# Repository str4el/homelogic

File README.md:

Homelogic
---------

Die Homelogic ist eine dezentral arbeitende __SPS Steuerung__, die für den Hausgebrauch gedacht ist. Es gibt verschiedene Hardware die mit der selben Firmware laufen. Die meisten sind für den direktem betrieb am Netz ausgelegt und haben mehrere digitale Ein- und Ausgänge.

Das Projekt besteht aus den Plänen für die _Hardware_, der _Firmware_ darin, einer _Bibliothek_ und einen darauf aufbauendem _Steuerprogramm_.

Die Steuerung ist SPS typisch frei programmierbar, als Sprache kommt dafür eine Variante von _Anweisungsliste_ zum Einsatz.

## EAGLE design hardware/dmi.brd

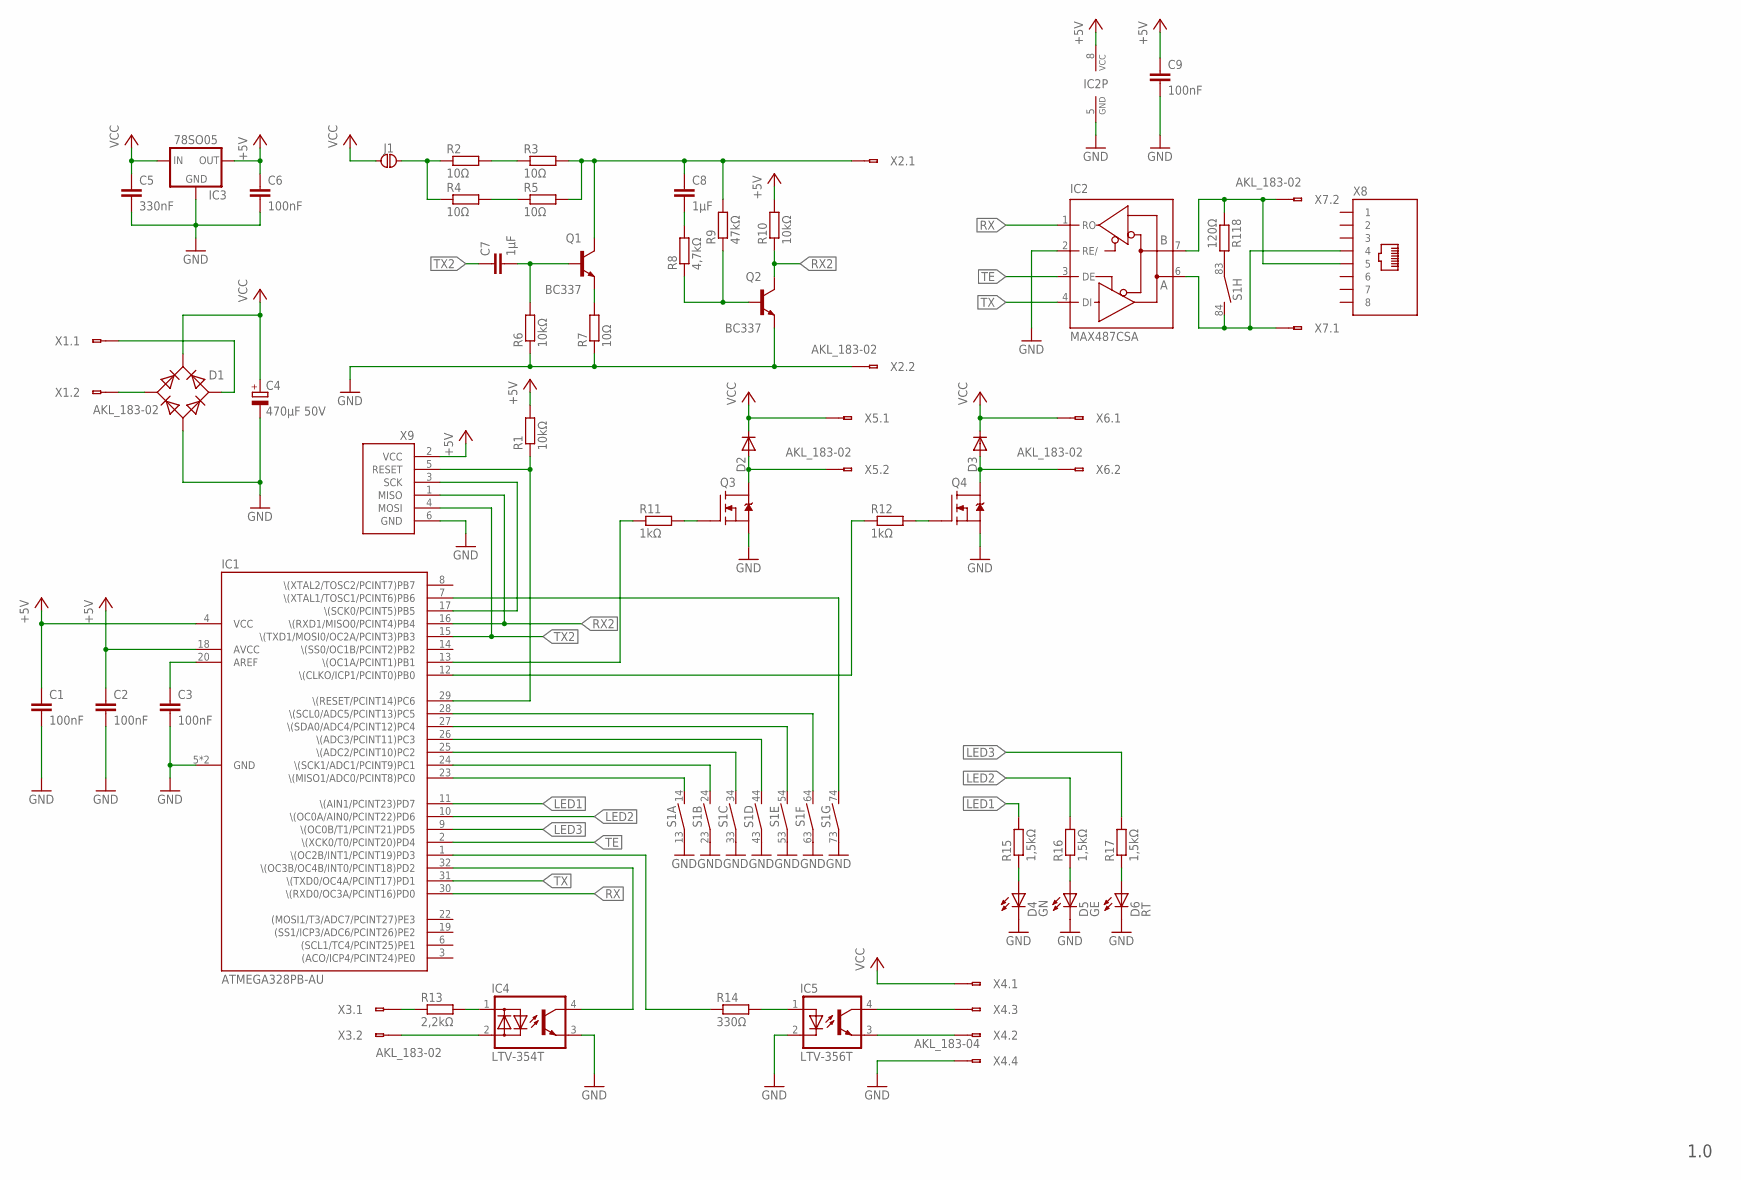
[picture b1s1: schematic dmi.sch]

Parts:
C1, C2, C3, C9: 100nF; CHIP_0603
C4: 470μF 50V; E5-13
C5: 330nF; CHIP_0805
C6: 100nF; CHIP_0805
C7, C8: 1μF; CHIP_1206
D1: GLEICHRICHTER-SDIP; SDIP04_508
D2, D3: DIODE-SOD123; SOD123
D4: GN; CHIP_0805
D5: GE; CHIP_0805
D6: RT; CHIP_0805
IC1: ATMEGA328PB-AU; QFP32_08
IC2: MAX487CSA; SOP08_127
IC3: 78SO05; SOP08_127
IC4: LTV-354T; SOP04_254
IC5: LTV-356T; SOP04_254
J1: JUMPER; JUMPER2
Q1, Q2: BC337; SOT23
Q3, Q4: N-MOS-SOT23-GSD; SOT23
R1, R6, R10: 10kΩ; CHIP_0603
R2, R3, R4, R5, R7: 10Ω; CHIP_1206
R8: 4,7kΩ; CHIP_0603
R9: 47kΩ; CHIP_0603
R11, R12: 1kΩ; CHIP_0603
R13: 2,2kΩ; CHIP_0603
R14: 330Ω; CHIP_0603
R15, R16, R17: 1,5kΩ; CHIP_0603
R118: 120Ω; CHIP_0805
S1: DP08D; DIP08_SMD
X1, X2, X3, X5, X6, X7: AKL_183-02
X4: AKL_183-04
X8: 8P8C; C-BMJ-0102
X9: ISP-AVR6; ML6

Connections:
+5V: C1.1, C2.1, C6.1, C9.1, IC1.4 (VCC), IC1.18 (AVCC), IC2.8 (VCC), IC3.1 (OUT), R1.2, R10.2, X9.2 (VCC)
GND: C1.2, C2.2, C3.2, C4.-, C5.2, C6.2, C9.2, D1.2 (-), D4.2 (C), D5.2 (C), D6.2 (C), IC1.5 (GND), IC1.21 (GND), IC2.2 (RE/), IC2.5 (GND), IC3.2 (GND), IC3.3 (GND), IC3.6 (GND), IC3.7 (GND), IC4.3 (E), IC5.2 (K), Q2.2 (E), Q3.2 (S), Q4.2 (S), R6.1, R7.1, S1.13 (3), S1.23 (3), S1.33 (3), S1.43 (3), S1.53 (3), S1.63 (3), S1.73 (3), X2.2, X4.4, X9.6 (GND)
LED1: IC1.11 (\(AIN1/PCINT23)PD7), R15.2
LED2: IC1.10 (\(OC0A/AIN0/PCINT22)PD6), R16.2
LED3: IC1.9 (\(OC0B/T1/PCINT21)PD5), R17.2
unnamed: IC1.32 (\(OC3B/OC4B/INT0/PCINT18)PD2), IC4.4 (C)
unnamed: IC4.2 (K), X3.2
unnamed: IC2.6 (A), S1.84 (4), X7.1, X8.P$4 (4)
unnamed: IC1.29 (\(RESET/PCINT14)PC6), R1.1, X9.5 (RESET)
unnamed: IC1.13 (\(OC1A/PCINT1)PB1), R11.1
unnamed: Q3.1 (G), R11.2
unnamed: D2.A, Q3.3 (D), X5.2
unnamed: IC5.3 (E), X4.2
unnamed: IC5.4 (C), X4.3
unnamed: IC1.1 (\(OC2B/INT1/PCINT19)PD3), R14.1
unnamed: IC5.1 (A), R14.2
unnamed: J1.P$2, R2.1, R4.1
unnamed: R2.2, R3.1
unnamed: R13.1, X3.1
unnamed: IC4.1 (A), R13.2
unnamed: Q1.2 (E), R7.2
unnamed: C7.2, Q1.1 (B), R6.2
unnamed: Q2.1 (B), R8.1, R9.1
unnamed: C8.2, R8.2
unnamed: D1.4 (AC2), X1.1
unnamed: C8.1, Q1.3 (C), R3.2, R5.2, R9.2, X2.1
unnamed: D1.3 (AC1), X1.2
unnamed: R4.2, R5.1
unnamed: Q4.1 (G), R12.2
unnamed: D3.A, Q4.3 (D), X6.2
unnamed: IC1.12 (\(CLKO/ICP1/PCINT0)PB0), R12.1
unnamed: IC2.7 (B), R118.1, X7.2, X8.P$5 (5)
unnamed: IC1.23 (\(MISO1/ADC0/PCINT8)PC0), S1.14 (4)
unnamed: IC1.24 (\(SCK1/ADC1/PCINT9)PC1), S1.24 (4)
unnamed: IC1.25 (\(ADC2/PCINT10)PC2), S1.34 (4)
unnamed: IC1.26 (\(ADC3/PCINT11)PC3), S1.44 (4)
unnamed: IC1.27 (\(SDA0/ADC4/PCINT12)PC4), S1.54 (4)
unnamed: R118.2, S1.83 (3)
unnamed: IC1.28 (\(SCL0/ADC5/PCINT13)PC5), S1.64 (4)
unnamed: IC1.7 (\(XTAL1/TOSC1/PCINT6)PB6), S1.74 (4)
unnamed: D6.1 (A), R17.1
unnamed: IC1.17 (\(SCK0/PCINT5)PB5), X9.3 (SCK)
unnamed: C3.1, IC1.20 (AREF)
unnamed: D4.1 (A), R15.1
unnamed: D5.1 (A), R16.1
RX: IC1.30 (\(RXD0/OC3A/PCINT16)PD0), IC2.1 (RO)
RX2: IC1.16 (\(RXD1/MISO0/PCINT4)PB4), Q2.3 (C), R10.1, X9.1 (MISO)
TE: IC1.2 (\(XCK0/T0/PCINT20)PD4), IC2.3 (DE)
TX: IC1.31 (\(TXD0/OC4A/PCINT17)PD1), IC2.4 (DI)
TX2: C7.1, IC1.15 (\(TXD1/MOSI0/OC2A/PCINT3)PB3), X9.4 (MOSI)
VCC: C4.+, C5.1, D1.1 (+), D2.K, D3.K, IC3.8 (IN), J1.P$1, X4.1, X5.1, X6.1

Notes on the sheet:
1.0

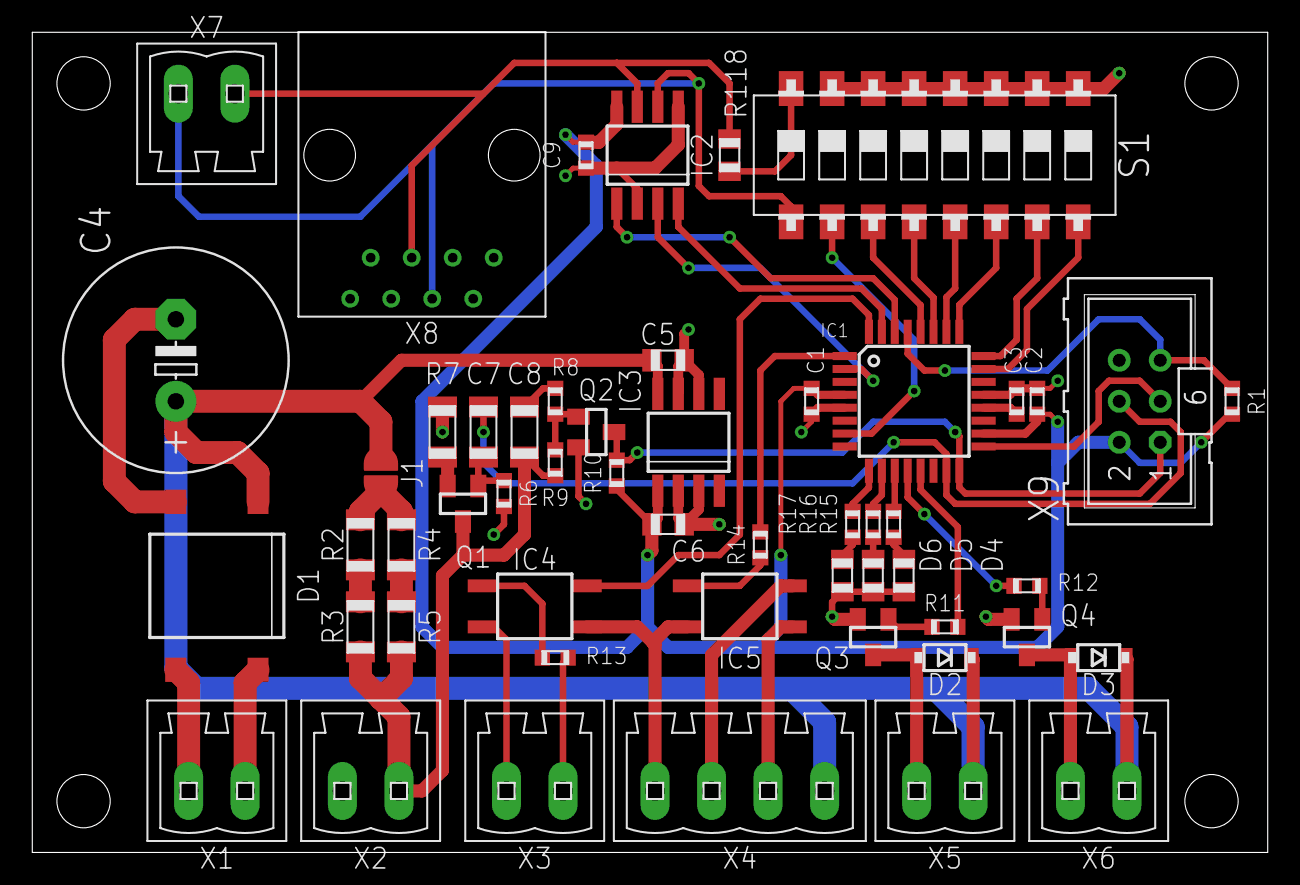
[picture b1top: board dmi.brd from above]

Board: 2 copper layers, 76.5 x 50.8 mm, 53 parts (0 on the bottom side), 51 nets.

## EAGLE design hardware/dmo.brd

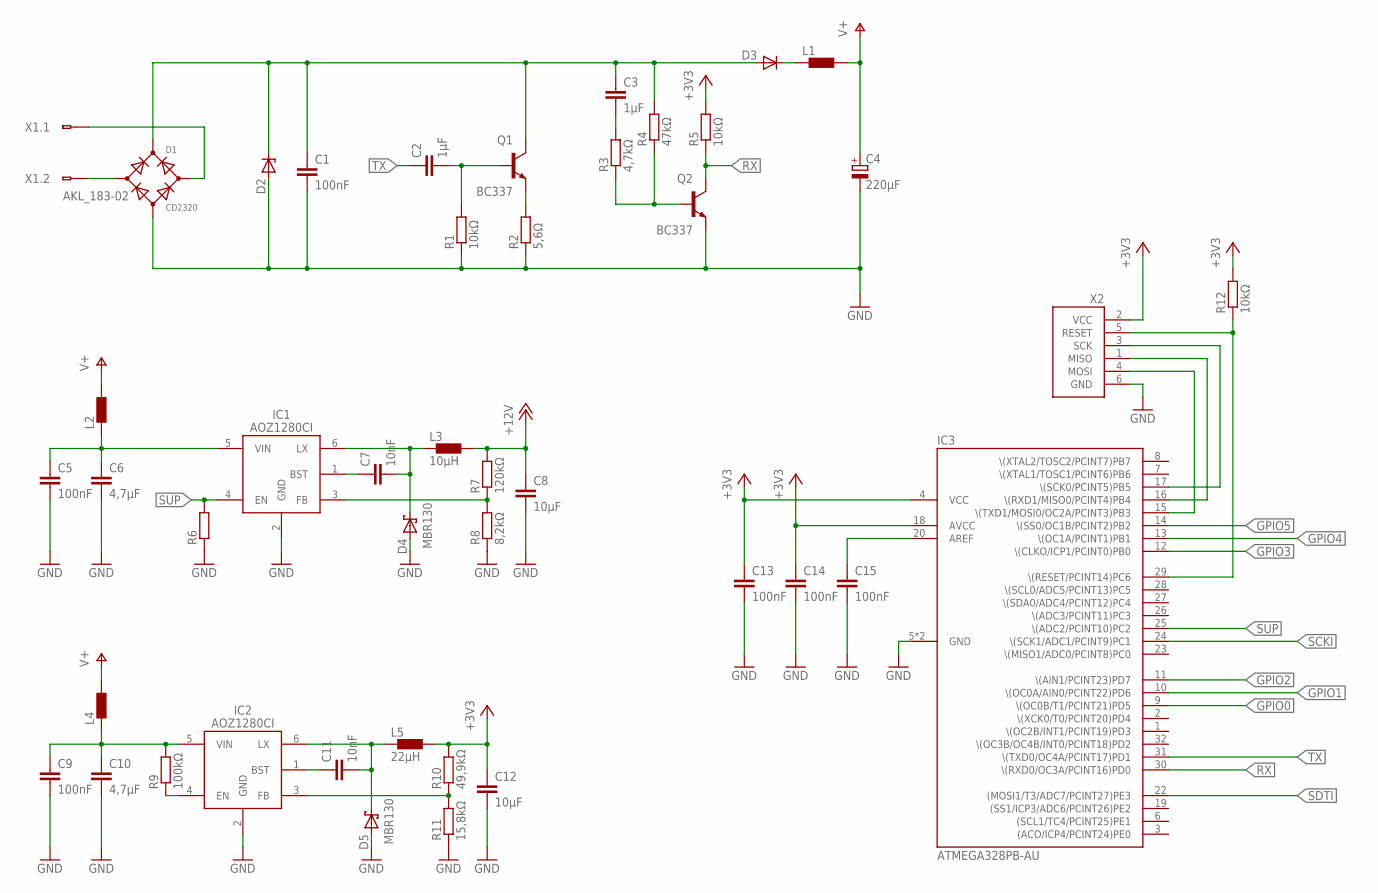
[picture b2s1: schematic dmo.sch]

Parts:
C1: 100nF; CHIP_1206
C2, C3: 1μF; CHIP_1206
C4: 220μF; E5-13
C5, C9: 100nF; CHIP_0805
C6, C10: 4,7μF; CHIP_1206
C7, C11: 10nF; CHIP_0603
C8, C12: 10μF; CHIP_1206
C13, C14, C15: 100nF; CHIP_0603
D1: CD2320; 2320
D2: Z-DIODE-SOD123; SOD123
D3: DIODE-SOD123; SOD123
D4, D5: MBR130; SOD123
IC1, IC2: AOZ1280CI; SOT23-6_095
IC3: ATMEGA328PB-AU; QFP32_08
L1, L2, L4: L_0805; CHIP_0805
L3: 10μH; CHIP_1210
L5: 22μH; CHIP_0805
Q1, Q2: BC337; SOT23
R1, R5, R12: 10kΩ; CHIP_0603
R2: 5,6Ω; CHIP_1206
R3: 4,7kΩ; CHIP_0603
R4: 47kΩ; CHIP_0603
R6: R_0603; CHIP_0603
R7: 120kΩ; CHIP_0603
R8: 8,2kΩ; CHIP_0603
R9: 100kΩ; CHIP_0603
R10: 49,9kΩ; CHIP_0603
R11: 15,8kΩ; CHIP_0603
X1: AKL_183-02
X2: ISP-AVR6; ML6

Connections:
+3V3: C12.1, C13.1, C14.1, IC3.4 (VCC), IC3.18 (AVCC), L5.1, R5.2, R10.2, R12.2, X2.2 (VCC)
+12V: C8.1, L3.1, R7.2
GND: C1.2, C4.-, C5.2, C6.2, C8.2, C9.2, C10.2, C12.2, C13.2, C14.2, C15.2, D1.-, D2.A, D4.A, D5.A, IC1.2 (GND), IC2.2 (GND), IC3.5 (GND), IC3.21 (GND), Q2.2 (E), R1.1, R2.1, R6.1, R8.1, R11.1, X2.6 (GND)
GPIO0: IC3.9 (\(OC0B/T1/PCINT21)PD5)
GPIO1: IC3.10 (\(OC0A/AIN0/PCINT22)PD6)
GPIO2: IC3.11 (\(AIN1/PCINT23)PD7)
GPIO3: IC3.12 (\(CLKO/ICP1/PCINT0)PB0)
GPIO4: IC3.13 (\(OC1A/PCINT1)PB1)
GPIO5: IC3.14 (\(SS0/OC1B/PCINT2)PB2)
unnamed: IC3.16 (\(RXD1/MISO0/PCINT4)PB4), X2.1 (MISO)
unnamed: IC3.15 (\(TXD1/MOSI0/OC2A/PCINT3)PB3), X2.4 (MOSI)
unnamed: D3.K, L1.2
unnamed: IC3.17 (\(SCK0/PCINT5)PB5), X2.3 (SCK)
unnamed: IC3.29 (\(RESET/PCINT14)PC6), R12.1, X2.5 (RESET)
unnamed: IC2.4 (EN), R9.1
unnamed: C11.1, IC2.1 (BST)
unnamed: C11.2, D5.K, IC2.6 (LX), L5.2
unnamed: IC2.3 (FB), R10.1, R11.2
unnamed: C9.1, C10.1, IC2.5 (VIN), L4.2, R9.2
unnamed: C7.1, IC1.1 (BST)
unnamed: C7.2, D4.K, IC1.6 (LX), L3.2
unnamed: IC1.3 (FB), R7.1, R8.2
unnamed: C5.1, C6.1, IC1.5 (VIN), L2.2
unnamed: C15.1, IC3.20 (AREF)
unnamed: Q1.2 (E), R2.2
unnamed: C2.2, Q1.1 (B), R1.2
unnamed: Q2.1 (B), R3.1, R4.1
unnamed: C3.2, R3.2
unnamed: D1.AC2, X1.1
unnamed: D1.AC1, X1.2
RX: IC3.30 (\(RXD0/OC3A/PCINT16)PD0), Q2.3 (C), R5.1
SCKI: IC3.24 (\(SCK1/ADC1/PCINT9)PC1)
SDTI: IC3.22 ((MOSI1/T3/ADC7/PCINT27)PE3)
SUP: IC1.4 (EN), IC3.25 (\(ADC2/PCINT10)PC2), R6.2
TX: C2.1, IC3.31 (\(TXD0/OC4A/PCINT17)PD1)
V+: C4.+, L1.1, L2.1, L4.1
VCC: C1.1, C3.1, D1.+, D2.K, D3.A, Q1.3 (C), R4.2

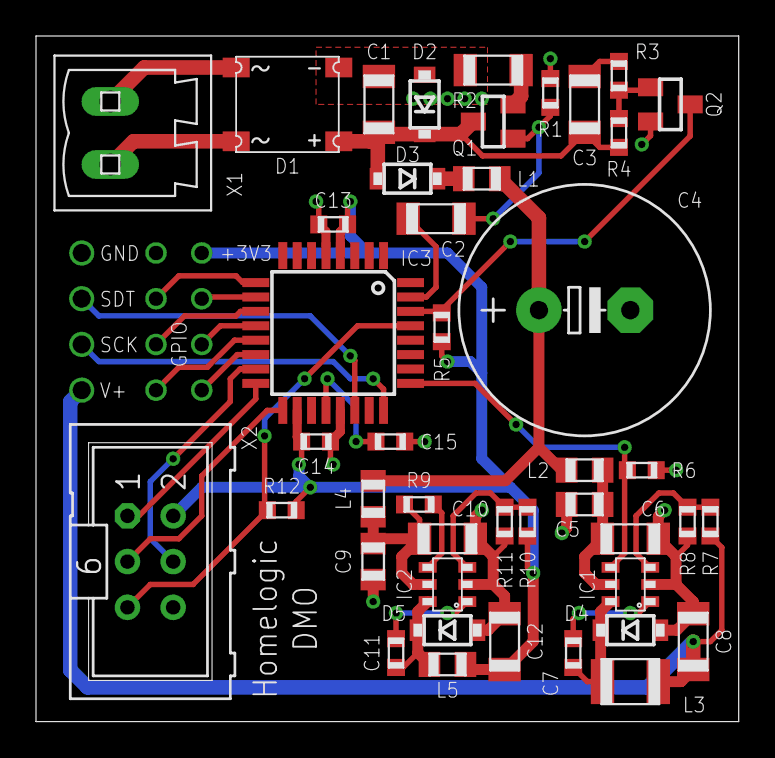
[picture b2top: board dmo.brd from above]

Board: 2 copper layers, 39.0 x 38.1 mm, 44 parts (0 on the bottom side), 29 nets.

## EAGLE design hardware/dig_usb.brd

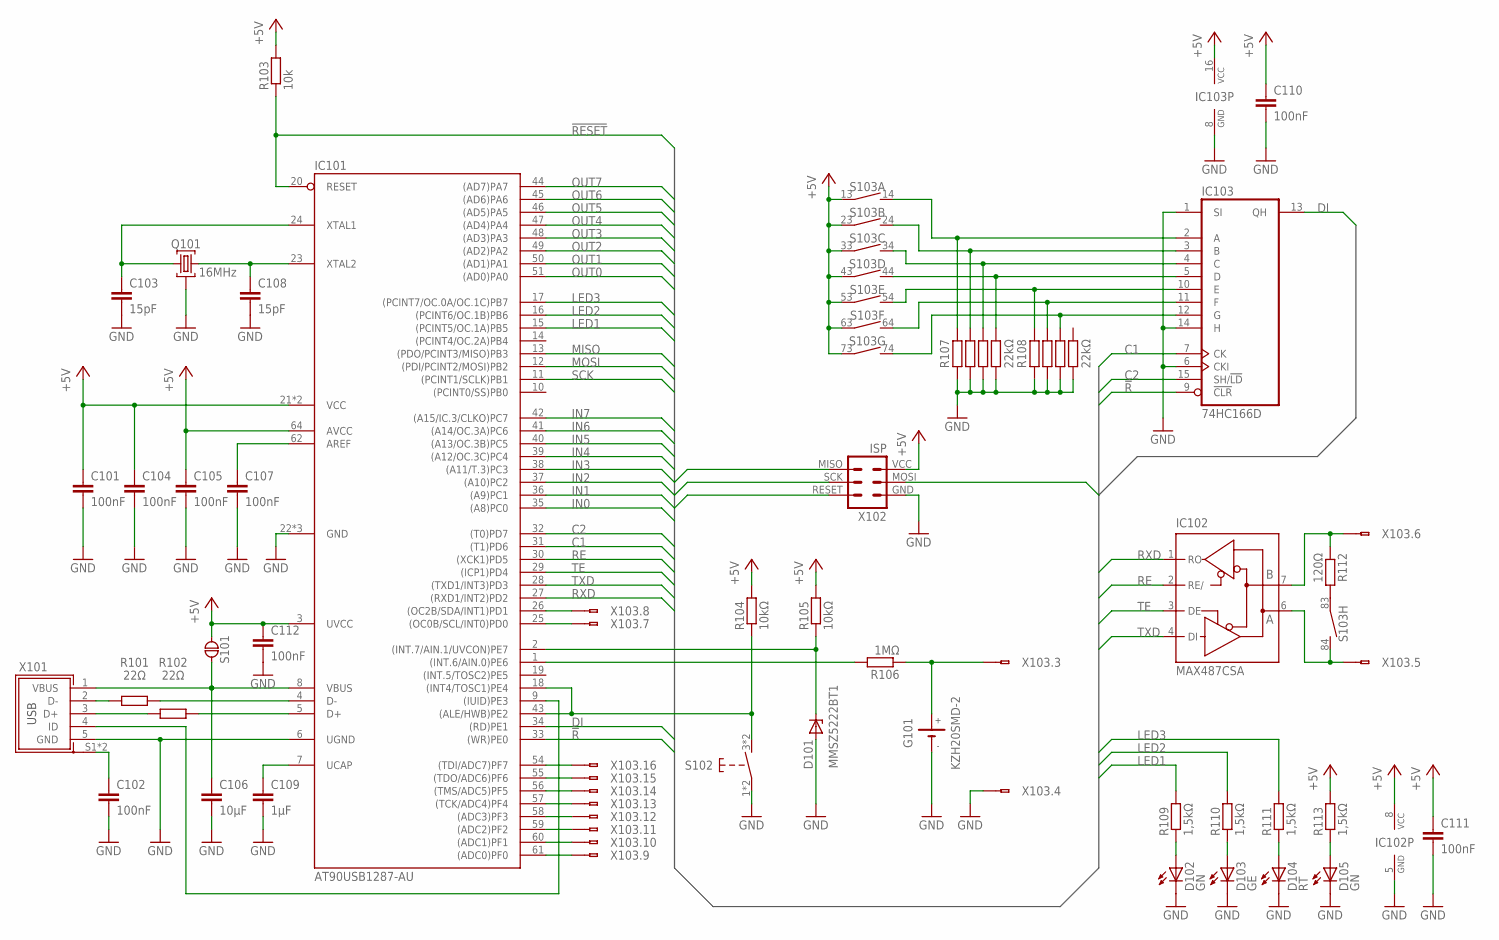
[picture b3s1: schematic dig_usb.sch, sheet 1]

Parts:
C101, C104, C105, C107, C110, C111, C112: 100nF; CHIP_0603
C102: 100nF; CHIP_0805
C103, C108: 15pF; CHIP_0805
C106: 10μF; CHIP_0805
C109: 1μF; CHIP_0805
D101: MMSZ5222BT1; SOD123
D102, D105: GN; CHIP_0805
D103: GE; CHIP_0805
D104: RT; CHIP_0805
G101: KZH20SMD-2; KHZ20SMD-2
IC101: AT90USB1287-AU; QFP64_08
IC102: MAX487CSA; SOP08_127
IC103: 74HC166D; SOP16_127
Q101: 16MHz; X22
R101, R102: 22Ω; CHIP_0805
R103: 10k; CHIP_0805
R104, R105: 10kΩ; CHIP_0805
R106: 1MΩ; CHIP_0805
R107, R108: 22kΩ; 1206
R109, R110, R111, R113: 1,5kΩ; CHIP_0805
R112: 120Ω; CHIP_0805
S101: JUMPER; JUMPER2
S102: KURZHUBS1; SCHURTER1301
S103: DP08D; DIP08_SMD
X101: USB-MINI-V; WE651005136421
X102: ISP; ML6
X103: WS34V

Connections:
!R: IC101.33 ((WR)PE0), IC103.9 (!CLR)
!RESET: IC101.20 (RESET), R103.1, X102.RESET
+5V: C101.1, C104.1, C105.1, C110.1, C111.1, C112.1, IC101.3 (UVCC), IC101.21 (VCC), IC101.52 (VCC), IC101.64 (AVCC), IC102.8 (VCC), IC103.16 (VCC), R103.2, R104.2, R105.2, R113.2, S101.P$1, S103.13 (3), S103.23 (3), S103.33 (3), S103.43 (3), S103.53 (3), S103.63 (3), S103.73 (3), X102.VCC; also elsewhere on the board
C1: IC101.31 ((T1)PD6), IC103.7 (CK)
C2: IC101.32 ((T0)PD7), IC103.15 (SH/!LD)
DI: IC101.34 ((RD)PE1), IC103.13 (QH)
GND: C101.2, C102.2, C103.2, C104.2, C105.2, C106.2, C107.2, C108.2, C109.2, C110.2, C111.2, C112.2, D101.A, D102.2 (C), D103.2 (C), D104.2 (C), D105.2 (C), G101.-, IC101.6 (UGND), IC101.22 (GND), IC101.53 (GND), IC101.63 (GND), IC102.5 (GND), IC103.1 (SI), IC103.6 (CKI), IC103.8 (GND), IC103.14 (H), Q101.2 (G), Q101.4 (G), R107.1A (1), R107.2A (3), R107.3A (5), R107.4A (7), R108.1A (1), R108.2A (3), R108.3A (5), R108.4A (7), S102.1, S102.2, X101.5 (GND), X102.GND, X103.4; also elsewhere on the board
IN0: IC101.35 ((A8)PC0); also elsewhere on the board
IN1: IC101.36 ((A9)PC1); also elsewhere on the board
IN2: IC101.37 ((A10)PC2); also elsewhere on the board
IN3: IC101.38 ((A11/T.3)PC3); also elsewhere on the board
IN4: IC101.39 ((A12/OC.3C)PC4); also elsewhere on the board
IN5: IC101.40 ((A13/OC.3B)PC5); also elsewhere on the board
IN6: IC101.41 ((A14/OC.3A)PC6); also elsewhere on the board
IN7: IC101.42 ((A15/IC.3/CLKO)PC7); also elsewhere on the board
LED1: IC101.15 ((PCINT5/OC.1A)PB5), R109.2
LED2: IC101.16 ((PCINT6/OC.1B)PB6), R110.2
LED3: IC101.17 ((PCINT7/OC.0A/OC.1C)PB7), R111.2
MISO: IC101.13 ((PDO/PCINT3/MISO)PB3), X102.MISO
MOSI: IC101.12 ((PDI/PCINT2/MOSI)PB2), X102.MOSI
unnamed: D104.1 (A), R111.1
unnamed: C107.1, IC101.62 (AREF)
unnamed: IC102.6 (A), S103.84 (4), X103.5
unnamed: IC101.1 ((INT.6/AIN.0)PE6), R106.2
unnamed: IC102.7 (B), R112.1, X103.6
unnamed: IC103.2 (A), R107.1B (2), S103.14 (4)
unnamed: IC103.3 (B), R107.2B (4), S103.24 (4)
unnamed: IC103.4 (C), R107.3B (6), S103.34 (4)
unnamed: IC103.5 (D), R107.4B (8), S103.44 (4)
unnamed: IC103.10 (E), R108.1B (2), S103.54 (4)
unnamed: IC103.11 (F), R108.2B (4), S103.64 (4)
unnamed: IC103.12 (G), R108.3B (6), S103.74 (4)
unnamed: R112.2, S103.83 (3)
unnamed: D105.1 (A), R113.1
unnamed: D102.1 (A), R109.1
unnamed: D103.1 (A), R110.1
unnamed: C109.1, IC101.7 (UCAP)
unnamed: R102.1, X101.3 (D+)
unnamed: IC101.5 (D+), R102.2
unnamed: R101.1, X101.2 (D-)
unnamed: IC101.4 (D-), R101.2
unnamed: IC101.9 ((IUID)PE3), X101.4 (ID)
unnamed: C106.1, IC101.8 (VBUS), S101.P$2, X101.1 (VBUS)
unnamed: C108.1, IC101.23 (XTAL2), Q101.3 (2)
unnamed: C103.1, IC101.24 (XTAL1), Q101.1
unnamed: D101.K, IC101.2 ((INT.7/AIN.1/UVCON)PE7), R105.1
unnamed: IC101.61 ((ADC0)PF0), X103.9
unnamed: IC101.60 ((ADC1)PF1), X103.10
unnamed: IC101.59 ((ADC2)PF2), X103.11
unnamed: IC101.58 ((ADC3)PF3), X103.12
unnamed: IC101.57 ((TCK/ADC4)PF4), X103.13
unnamed: IC101.56 ((TMS/ADC5)PF5), X103.14
unnamed: IC101.55 ((TDO/ADC6)PF6), X103.15
unnamed: IC101.54 ((TDI/ADC7)PF7), X103.16
unnamed: G101.+, R106.1, X103.3
unnamed: IC101.25 ((OC0B/SCL/INT0)PD0), X103.7
unnamed: IC101.26 ((OC2B/SDA/INT1)PD1), X103.8
unnamed: IC101.18 ((INT4/TOSC1)PE4), IC101.43 ((ALE/HWB)PE2), R104.1, S102.3 (S), S102.4 (S)
OUT0: IC101.51 ((AD0)PA0); also elsewhere on the board
OUT1: IC101.50 ((AD1)PA1); also elsewhere on the board
OUT2: IC101.49 ((AD2)PA2); also elsewhere on the board
OUT3: IC101.48 ((AD3)PA3); also elsewhere on the board
OUT4: IC101.47 ((AD4)PA4); also elsewhere on the board
OUT5: IC101.46 ((AD5)PA5); also elsewhere on the board
OUT6: IC101.45 ((AD6)PA6); also elsewhere on the board
OUT7: IC101.44 ((AD7)PA7); also elsewhere on the board
RE: IC101.30 ((XCK1)PD5), IC102.2 (RE/)
RXD: IC101.27 ((RXD1/INT2)PD2), IC102.1 (RO)
SCK: IC101.11 ((PCINT1/SCLK)PB1), X102.SCK
TE: IC101.29 ((ICP1)PD4), IC102.3 (DE)
TXD: IC101.28 ((TXD1/INT3)PD3), IC102.4 (DI)
USHIELD: C102.1, X101.S1 (SHIELD), X101.S2 (SHIELD)

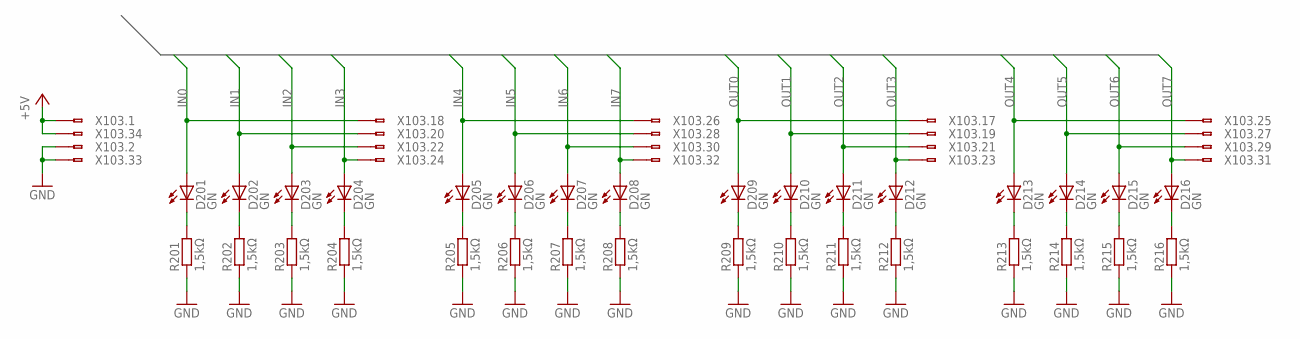
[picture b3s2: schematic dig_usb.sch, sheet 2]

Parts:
D201, D202, D203, D204, D205, D206, D207, D208, D209, D210, D211, D212, D213, D214, D215, D216: GN; CHIP_0805
R201, R202, R203, R204, R205, R206, R207, R208, R209, R210, R211, R212, R213, R214, R215, R216: 1,5kΩ; CHIP_0805
X103: WS34V

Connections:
+5V: X103.1, X103.34; also elsewhere on the board
GND: R201.1, R202.1, R203.1, R204.1, R205.1, R206.1, R207.1, R208.1, R209.1, R210.1, R211.1, R212.1, R213.1, R214.1, R215.1, R216.1, X103.2, X103.33; also elsewhere on the board
IN0: D201.1 (A), X103.18; also elsewhere on the board
IN1: D202.1 (A), X103.20; also elsewhere on the board
IN2: D203.1 (A), X103.22; also elsewhere on the board
IN3: D204.1 (A), X103.24; also elsewhere on the board
IN4: D205.1 (A), X103.26; also elsewhere on the board
IN5: D206.1 (A), X103.28; also elsewhere on the board
IN6: D207.1 (A), X103.30; also elsewhere on the board
IN7: D208.1 (A), X103.32; also elsewhere on the board
unnamed: D201.2 (C), R201.2
unnamed: D202.2 (C), R202.2
unnamed: D203.2 (C), R203.2
unnamed: D204.2 (C), R204.2
unnamed: D205.2 (C), R205.2
unnamed: D206.2 (C), R206.2
unnamed: D207.2 (C), R207.2
unnamed: D208.2 (C), R208.2
unnamed: D209.2 (C), R209.2
unnamed: D210.2 (C), R210.2
unnamed: D211.2 (C), R211.2
unnamed: D212.2 (C), R212.2
unnamed: D213.2 (C), R213.2
unnamed: D214.2 (C), R214.2
unnamed: D215.2 (C), R215.2
unnamed: D216.2 (C), R216.2
OUT0: D209.1 (A), X103.17; also elsewhere on the board
OUT1: D210.1 (A), X103.19; also elsewhere on the board
OUT2: D211.1 (A), X103.21; also elsewhere on the board
OUT3: D212.1 (A), X103.23; also elsewhere on the board
OUT4: D213.1 (A), X103.25; also elsewhere on the board
OUT5: D214.1 (A), X103.27; also elsewhere on the board
OUT6: D215.1 (A), X103.29; also elsewhere on the board
OUT7: D216.1 (A), X103.31; also elsewhere on the board

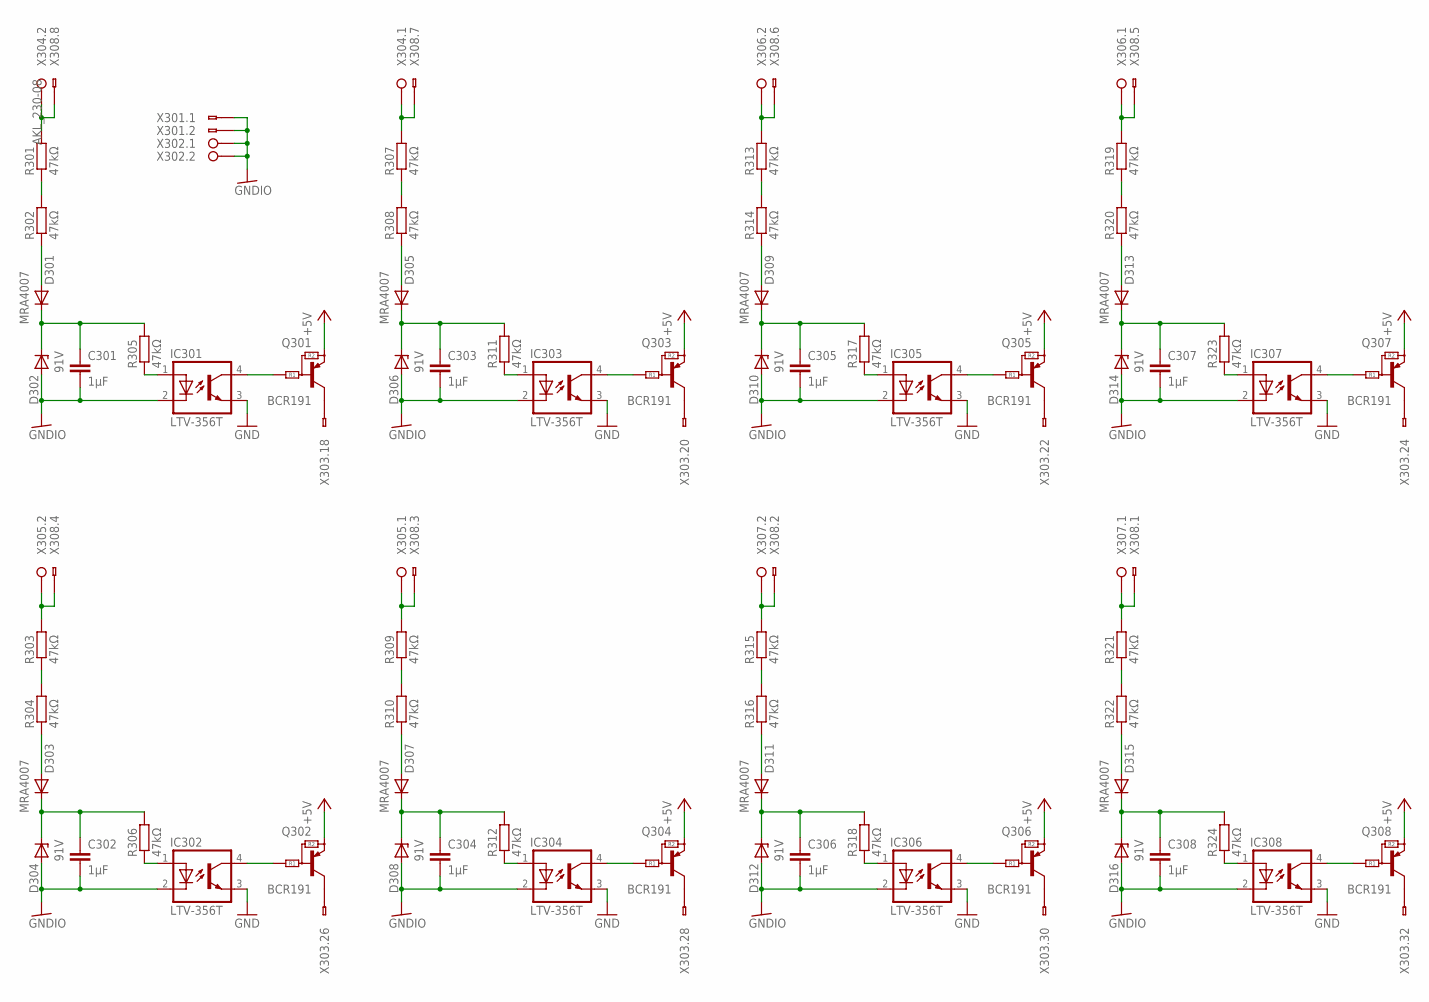
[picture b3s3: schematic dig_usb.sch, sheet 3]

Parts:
C301, C302, C303, C304, C305, C306, C307, C308: 1μF; CHIP_1206
D301, D303, D305, D307, D309, D311, D313, D315: MRA4007; DO214AC
D302, D304, D306, D308, D310, D312, D314, D316: 91V; SOD123
IC301, IC302, IC303, IC304, IC305, IC306, IC307, IC308: LTV-356T; SOP04_254
Q301, Q302, Q303, Q304, Q305, Q306, Q307, Q308: BCR191; SOT23
R301, R302, R303, R304, R305, R306, R307, R308, R309, R310, R311, R312, R313, R314, R315, R316, R317, R318, R319, R320, R321, R322, R323, R324: 47kΩ; CHIP_1206
X301: AKL_230-02
X302, X304, X305, X306, X307: RIA-73-02
X303: WS34V
X308: AKL_230-08

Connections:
+5V: Q301.2 (E), Q302.2 (E), Q303.2 (E), Q304.2 (E), Q305.2 (E), Q306.2 (E), Q307.2 (E), Q308.2 (E); also elsewhere on the board
GND: IC301.3 (E), IC302.3 (E), IC303.3 (E), IC304.3 (E), IC305.3 (E), IC306.3 (E), IC307.3 (E), IC308.3 (E); also elsewhere on the board
GNDIO: C301.2, C302.2, C303.2, C304.2, C305.2, C306.2, C307.2, C308.2, D302.A, D304.A, D306.A, D308.A, D310.A, D312.A, D314.A, D316.A, IC301.2 (K), IC302.2 (K), IC303.2 (K), IC304.2 (K), IC305.2 (K), IC306.2 (K), IC307.2 (K), IC308.2 (K), X301.P$1, X301.P$2, X302.1, X302.2; also elsewhere on the board
unnamed: R301.1, R302.2
unnamed: D301.A, R302.1
unnamed: C301.1, D301.K, D302.K, R305.2
unnamed: IC301.1 (A), R305.1
unnamed: D305.A, R308.1
unnamed: C303.1, D305.K, D306.K, R311.2
unnamed: IC303.1 (A), R311.1
unnamed: D309.A, R314.1
unnamed: C305.1, D309.K, D310.K, R317.2
unnamed: IC305.1 (A), R317.1
unnamed: D313.A, R320.1
unnamed: C307.1, D313.K, D314.K, R323.2
unnamed: R307.1, R308.2
unnamed: R313.1, R314.2
unnamed: IC307.1 (A), R323.1
unnamed: D303.A, R304.1
unnamed: C302.1, D303.K, D304.K, R306.2
unnamed: IC302.1 (A), R306.1
unnamed: D307.A, R310.1
unnamed: C304.1, D307.K, D308.K, R312.2
unnamed: R319.1, R320.2
unnamed: R307.2, X304.1, X308.P$7
unnamed: R301.2, X304.2, X308.P$8
unnamed: R319.2, X306.1, X308.P$5
unnamed: R313.2, X306.2, X308.P$6
unnamed: R303.1, R304.2
unnamed: R309.1, R310.2
unnamed: IC307.4 (C), Q307.1 (B)
unnamed: R315.1, R316.2
unnamed: R321.1, R322.2
unnamed: IC304.1 (A), R312.1
unnamed: R303.2, X305.2, X308.P$4
unnamed: D311.A, R316.1
unnamed: R309.2, X305.1, X308.P$3
unnamed: R321.2, X307.1, X308.P$1
unnamed: R315.2, X307.2, X308.P$2
unnamed: C306.1, D311.K, D312.K, R318.2
unnamed: IC306.1 (A), R318.1
unnamed: IC305.4 (C), Q305.1 (B)
unnamed: D315.A, R322.1
unnamed: IC303.4 (C), Q303.1 (B)
unnamed: IC301.4 (C), Q301.1 (B)
unnamed: C308.1, D315.K, D316.K, R324.2
unnamed: IC302.4 (C), Q302.1 (B)
unnamed: IC304.4 (C), Q304.1 (B)
unnamed: IC306.4 (C), Q306.1 (B)
unnamed: IC308.4 (C), Q308.1 (B)
unnamed: IC308.1 (A), R324.1
unnamed: Q301.3 (C), X303.18
unnamed: Q303.3 (C), X303.20
unnamed: Q305.3 (C), X303.22
unnamed: Q307.3 (C), X303.24
unnamed: Q302.3 (C), X303.26
unnamed: Q304.3 (C), X303.28
unnamed: Q306.3 (C), X303.30
unnamed: Q308.3 (C), X303.32

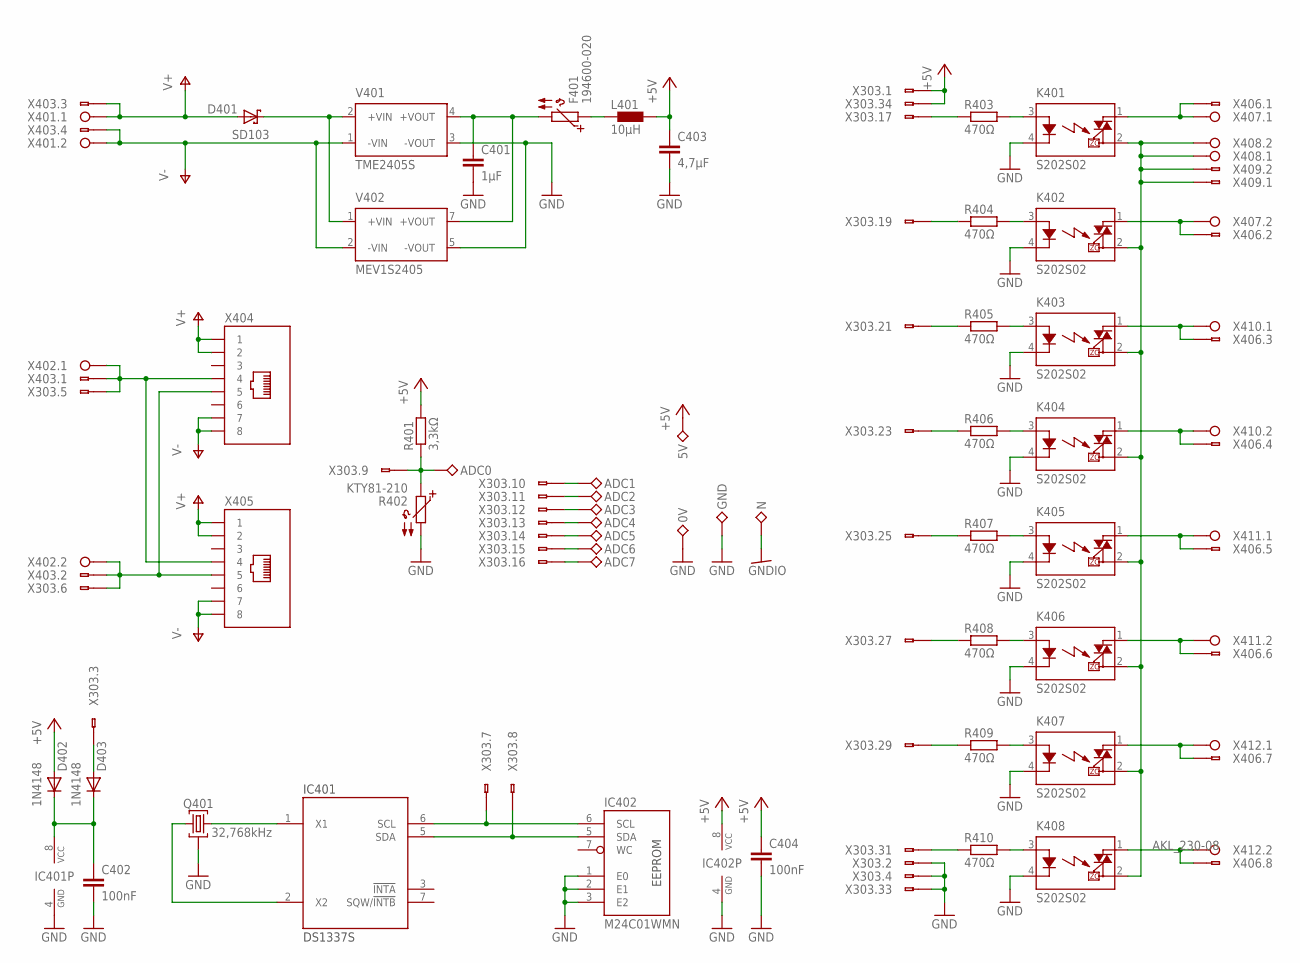
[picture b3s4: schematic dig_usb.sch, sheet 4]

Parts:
0V, 5V: TEST_VIA_08; VIA08
ADC0, ADC1, ADC2, ADC3, ADC4, ADC5, ADC6, ADC7: TEST_PAD_SMALL; PADS
C401: 1μF; CHIP_0805
C402, C404: 100nF; CHIP_0603
C403: 4,7μF; CHIP_0805
D401: SD103; SOD123
D402, D403: 1N4148; SOD123
F401: 194600-020; CHIP_1812
GND: TEST_VIA_08; VIA08
IC401: DS1337S; SOP08_127
IC402: M24C01WMN; SOP08_127
K401, K402, K403, K404, K405, K406, K407, K408: S202S02; SIP4
L401: 10μH; 1812AF
N: TEST_VIA_08; VIA08
Q401: 32,768kHz; MS1V-T1K
R401: 3,3kΩ; CHIP_0805
R402: KTY81-210; TO92
R403, R404, R405, R406, R407, R408, R409, R410: 470Ω; CHIP_0805
V401: TME2405S; TME-24V; MPN TME 2405S
V402: MEV1S2405; MEV1S
X303: WS34V
X401, X402, X407, X408, X410, X411, X412: RIA-73-02
X403: AKL_230-04
X404, X405: 8P8C; C-BMJ-0102
X406: AKL_230-08
X409: AKL_230-02

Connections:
+5V: 5V.1, C403.1, C404.1, D402.A, IC402.8 (VCC), L401.1, R401.2, X303.1, X303.34; also elsewhere on the board
GND: 0V.1, C401.2, C402.2, C403.2, C404.2, GND.1, IC401.4 (GND), IC402.1 (E0), IC402.2 (E1), IC402.3 (E2), IC402.4 (GND), K401.4 (K), K402.4 (K), K403.4 (K), K404.4 (K), K405.4 (K), K406.4 (K), K407.4 (K), K408.4 (K), Q401.G, R402.2, V401.3 (-VOUT), V402.5 (-VOUT), X303.2, X303.4, X303.33; also elsewhere on the board
GNDIO: N.1; also elsewhere on the board
L: K401.2 (DS2), K402.2 (DS2), K403.2 (DS2), K404.2 (DS2), K405.2 (DS2), K406.2 (DS2), K407.2 (DS2), K408.2 (DS2), X408.1, X408.2, X409.P$1, X409.P$2
unnamed: K401.3 (A), R403.2
unnamed: K402.3 (A), R404.2
unnamed: C401.1, F401.2, V401.4 (+VOUT), V402.7 (+VOUT)
unnamed: D401.K, V401.2 (+VIN), V402.1 (+VIN)
unnamed: F401.1, L401.2
unnamed: K403.3 (A), R405.2
unnamed: K404.3 (A), R406.2
unnamed: ADC1.1, X303.10
unnamed: K405.3 (A), R407.2
unnamed: K406.3 (A), R408.2
unnamed: K407.3 (A), R409.2
unnamed: C402.1, D402.K, D403.K, IC401.8 (VCC)
unnamed: K408.3 (A), R410.2
unnamed: R403.1, X303.17
unnamed: K401.1 (DS1), X406.P$1, X407.1
unnamed: K402.1 (DS1), X406.P$2, X407.2
unnamed: K403.1 (DS1), X406.P$3, X410.1
unnamed: K404.1 (DS1), X406.P$4, X410.2
unnamed: K405.1 (DS1), X406.P$5, X411.1
unnamed: R404.1, X303.19
unnamed: K406.1 (DS1), X406.P$6, X411.2
unnamed: K407.1 (DS1), X406.P$7, X412.1
unnamed: R405.1, X303.21
unnamed: R406.1, X303.23
unnamed: K408.1 (DS1), X406.P$8, X412.2
unnamed: R407.1, X303.25
unnamed: R408.1, X303.27
unnamed: R409.1, X303.29
unnamed: R410.1, X303.31
unnamed: IC401.1 (X1), Q401.2
unnamed: IC401.2 (X2), Q401.1
unnamed: D403.A, X303.3
unnamed: IC401.6 (SCL), IC402.6 (SCL), X303.7
unnamed: IC401.5 (SDA), IC402.5 (SDA), X303.8
unnamed: X303.6, X402.2, X403.P$2, X404.P$5 (5), X405.P$5 (5)
unnamed: X303.5, X402.1, X403.P$1, X404.P$4 (4), X405.P$4 (4)
unnamed: ADC0.1, R401.1, R402.1, X303.9
unnamed: ADC2.1, X303.11
unnamed: ADC3.1, X303.12
unnamed: ADC4.1, X303.13
unnamed: ADC5.1, X303.14
unnamed: ADC6.1, X303.15
unnamed: ADC7.1, X303.16
V+: D401.A, X401.1, X403.P$3, X404.P$1 (1), X404.P$2 (2), X405.P$1 (1), X405.P$2 (2)
V-: V401.1 (-VIN), V402.2 (-VIN), X401.2, X403.P$4, X404.P$7 (7), X404.P$8 (8), X405.P$7 (7), X405.P$8 (8)
